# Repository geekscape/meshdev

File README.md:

meshdev
=======

MeshThing and related development: Hardware and Software

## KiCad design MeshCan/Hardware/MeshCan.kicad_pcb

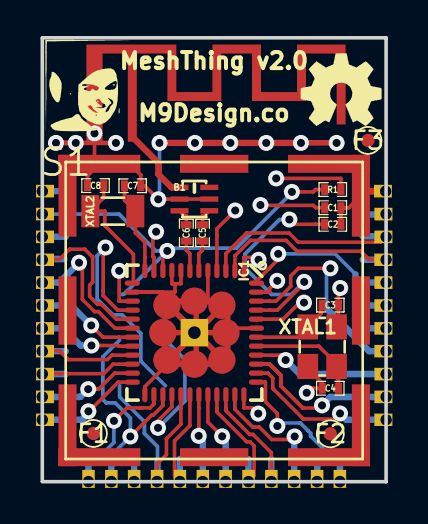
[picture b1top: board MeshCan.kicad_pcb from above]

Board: 4 copper layers, 19.1 x 24.7 mm, 21 parts (1 on the bottom side), 45 nets.

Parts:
A1: ANTENNA; _MT_IFA-2.4GHzPCBAntenna
B1: Balun; _MT_Wuerth748421245-A
C1, C2: 100n; SM0402_c
C3, C4: 10p; SM0402_c
C5, C6, C7, C8: 22p; SM0402_c
F1, F2, F3: CONN_1; _MT_Fiducial
H1: ICSP; _MC_pin_pad_3x2
IC1: ATMEGA2564/1284/644RFR2; _MT_QFN50P700X700-49N-MeshThingWPadVias
P1: CONN34; _MC_CanFootprint-34Pin
PrettyLady: PrettyLady; _MC_LOGO-PrettyLady
R1: 10k; SM0402_r
S1: RFShield; _MT_MC_EMIShield-16.5x16.5
XTAL1: CRYSTAL_SMD-TSX3225; 16MHz-3.2x2.5mm-TSX-3225
XTAL2: 32kHz; _MC_TF32D-32768-Crystal

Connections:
+3.3V: H1.2, IC1.16, IC1.44, P1.1, R1.1
GND: A1.2, B1.2, B1.5, C1.2, C2.2, C3.2, C4.2, C7.2, C8.2, H1.6, IC1.5, IC1.8, IC1.9, IC1.14, IC1.25, IC1.43, IC1.49, P1.34, XTAL1.2, XTAL1.4
MISO: H1.1, IC1.29, P1.15
MOSI: H1.4, IC1.28, P1.14
unnamed: A1.1, B1.1
unnamed: B1.3, C6.1
unnamed: B1.4, C5.1
unnamed: C1.1, IC1.15
unnamed: C2.1, IC1.45
unnamed: C3.1, IC1.42, XTAL1.1
unnamed: C4.1, IC1.41, XTAL1.3
unnamed: C5.2, IC1.6
unnamed: C6.2, IC1.7
unnamed: C7.1, IC1.12, XTAL2.2
unnamed: C8.1, IC1.13, XTAL2.1
PB0/SS: IC1.26, P1.12
PB4: IC1.30, P1.16
PB5: IC1.31, P1.17
PB6: IC1.32, P1.18
PB7: IC1.33, P1.19
PD4: IC1.21, P1.8
PD5: IC1.22, P1.9
PD6: IC1.23, P1.10
PD7: IC1.24, P1.11
PE2: IC1.36, P1.22
PE3: IC1.37, P1.23
PE4: IC1.38, P1.24
PE5: IC1.39, P1.25
PE7: IC1.40, P1.26
PF0: IC1.46, P1.27
PF1: IC1.47, P1.28
PF2: IC1.48, P1.29
PF3-4: IC1.1, P1.30
PF5: IC1.2, P1.31
PF6: IC1.3, P1.32
PF7: IC1.4, P1.33
PG1: IC1.11, P1.3
RX0: IC1.34, P1.20
RX1: IC1.19, P1.6
Reset: H1.5, IC1.10, P1.2, R1.2
SCK: H1.3, IC1.27, P1.13
SCL: IC1.17, P1.4
SDA: IC1.18, P1.5
TX0: IC1.35, P1.21
TX1: IC1.20, P1.7

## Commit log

2013-12-20 Initial MeshCan commit.
2013-12-20 Import traces, minor movements, .gitignore.
2013-12-22 GND/PWR planes. Trace cleanup and anchor traces to TH pads.
2013-12-22 Approaching layout finish. Transitioning to meshthing repo.

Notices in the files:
MeshCan/Hardware/MeshCan.kicad_pcb:
© M9Design.co 2013
